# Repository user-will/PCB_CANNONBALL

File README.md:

# REIL INDUSTRIAL - CANNONBALL

A feature-packed ESP32-C3 development board built around the **ESP32-C3-WROOM-02-N4**, designed to be the last board you need for any project — smart home device, RC car, wearable, or anything else you can dream up.

The big pitch: pull a single-cell LiPo or Li-ion from an old vape, plug it into the JST PH connector, and go. The board handles charging, protection, and fuel gauging — no external circuitry needed.

---

## Features

- **MCU** — ESP32-C3-WROOM-02-N4 (RISC-V, 2.4 GHz Wi-Fi + BLE, 4 MB flash)
- **USB protection** — USBLC6-4SC6 TVS diode array on the USB lines
- **Battery charging** — BQ24075RGT linear charger (100 mA default, 500 mA selectable via GPIO)
- **Battery protection** — DW01A + FS8205A dual MOSFET pack (over-charge, over-discharge, short circuit)
- **Battery monitoring** — MAX17048 fuel gauge over I2C with low-battery alert
- **3.3 V regulation** — AP2112K-3.3 LDO
- **Addressable LEDs** — SK6812-EC20 RGB LEDs switched via DMG2301L MOSFET
- **IMU** — LSM6DS3 (6-axis accelerometer + gyroscope, I2C)
- **Temp & humidity** — SHT40 (I2C)
- **Light sensor** — VEML6030 ambient light sensor (I2C)
- **I2C expansion** — JST SH 1.0 mm 4-pin connector (3.3 V, GND, SDA, SCL)
- **Battery connector** — JST PH 2.0 mm 2-pin

---

## Power

| Rail | Source | Voltage | Notes |
|------|--------|---------|-------|
| USB-C | External | 5 V nominal, **6 V max** | Limited by AP2112K-3.3 LDO max input. Do not exceed 6 V on the 5 V pins or USB input. |
| 5V pin (J5/J6) | External or VBUS | 5 V nominal, **6 V max** | Same rail as USB VBUS — feeds the LDO and charger directly. |
| 3V3 pin (J4/J6) | AP2112K-3.3 LDO | **3.3 V exactly** | If powering the board externally via the 3V3 pin (bypassing the LDO), supply a regulated 3.3 V. The ESP32 and all peripherals run at 3.3 V with a ±0.3 V tolerance — do not exceed 3.6 V or drop below 3.0 V. |

---

## Pin Reference

| GPIO | Function | Notes |
|------|----------|-------|
| 3 | MAX17048 alert | Active-low interrupt when battery is low |
| 4 | SK6812 data | Addressable LED data line |
| 5 | LED enable (MOSFET) | Pull **high** to enable LEDs, low to disable |
| 10 | BQ24075 EN1 (charge rate) | Pull **high** to increase charge current from 100 mA to 500 mA |

---

## Bill of Materials

| Reference | Part | Function |
|-----------|------|----------|
| U1 | ESP32-C3-WROOM-02-N4 | Main MCU |
| U2 | BQ24075RGT | Li-ion/LiPo battery charger |
| U3 | MAX17048 | Battery fuel gauge (I2C) |
| U4 | DW01A | Battery protection IC |
| U5 | FS8205A | Dual MOSFET for battery protection |
| U6 | AP2112K-3.3 | 3.3 V LDO regulator |
| U7 | USBLC6-4SC6 | USB ESD/TVS protection |
| U8 | LSM6DS3 | 6-axis IMU (I2C) |
| U9 | SHT40 | Temperature & humidity sensor (I2C) |
| U10 | VEML6030 | Ambient light sensor (I2C) |
| Q3 | 2N7002K | N-channel MOSFET (LED power switch) |
| LED1+ | SK6812-EC20 | Addressable RGB LEDs |

---

## Opening in KiCad

1. Clone or download this repo
2. Open KiCad and select **File → Open Project**
3. Navigate to the repo folder and open `CANNONBALL.kicad_pro`

All schematic symbols and footprints are either embedded in the project files or included in the `jlcpcb.pretty/` and `jlcpcb.kicad_sym` local libraries — no additional library setup required.

---

## Battery Compatibility

Any single-cell LiPo or Li-ion (3.6–4.2 V nominal) will work. The onboard protection circuit guards against:
- Over-charge (> 4.2 V)
- Over-discharge (< 2.5 V)
- Short circuit / over-current

Cells salvaged from vapes, old phones, or RC packs all work fine. Use the JST PH 2.0 mm 2-pin connector (positive on pin 1).

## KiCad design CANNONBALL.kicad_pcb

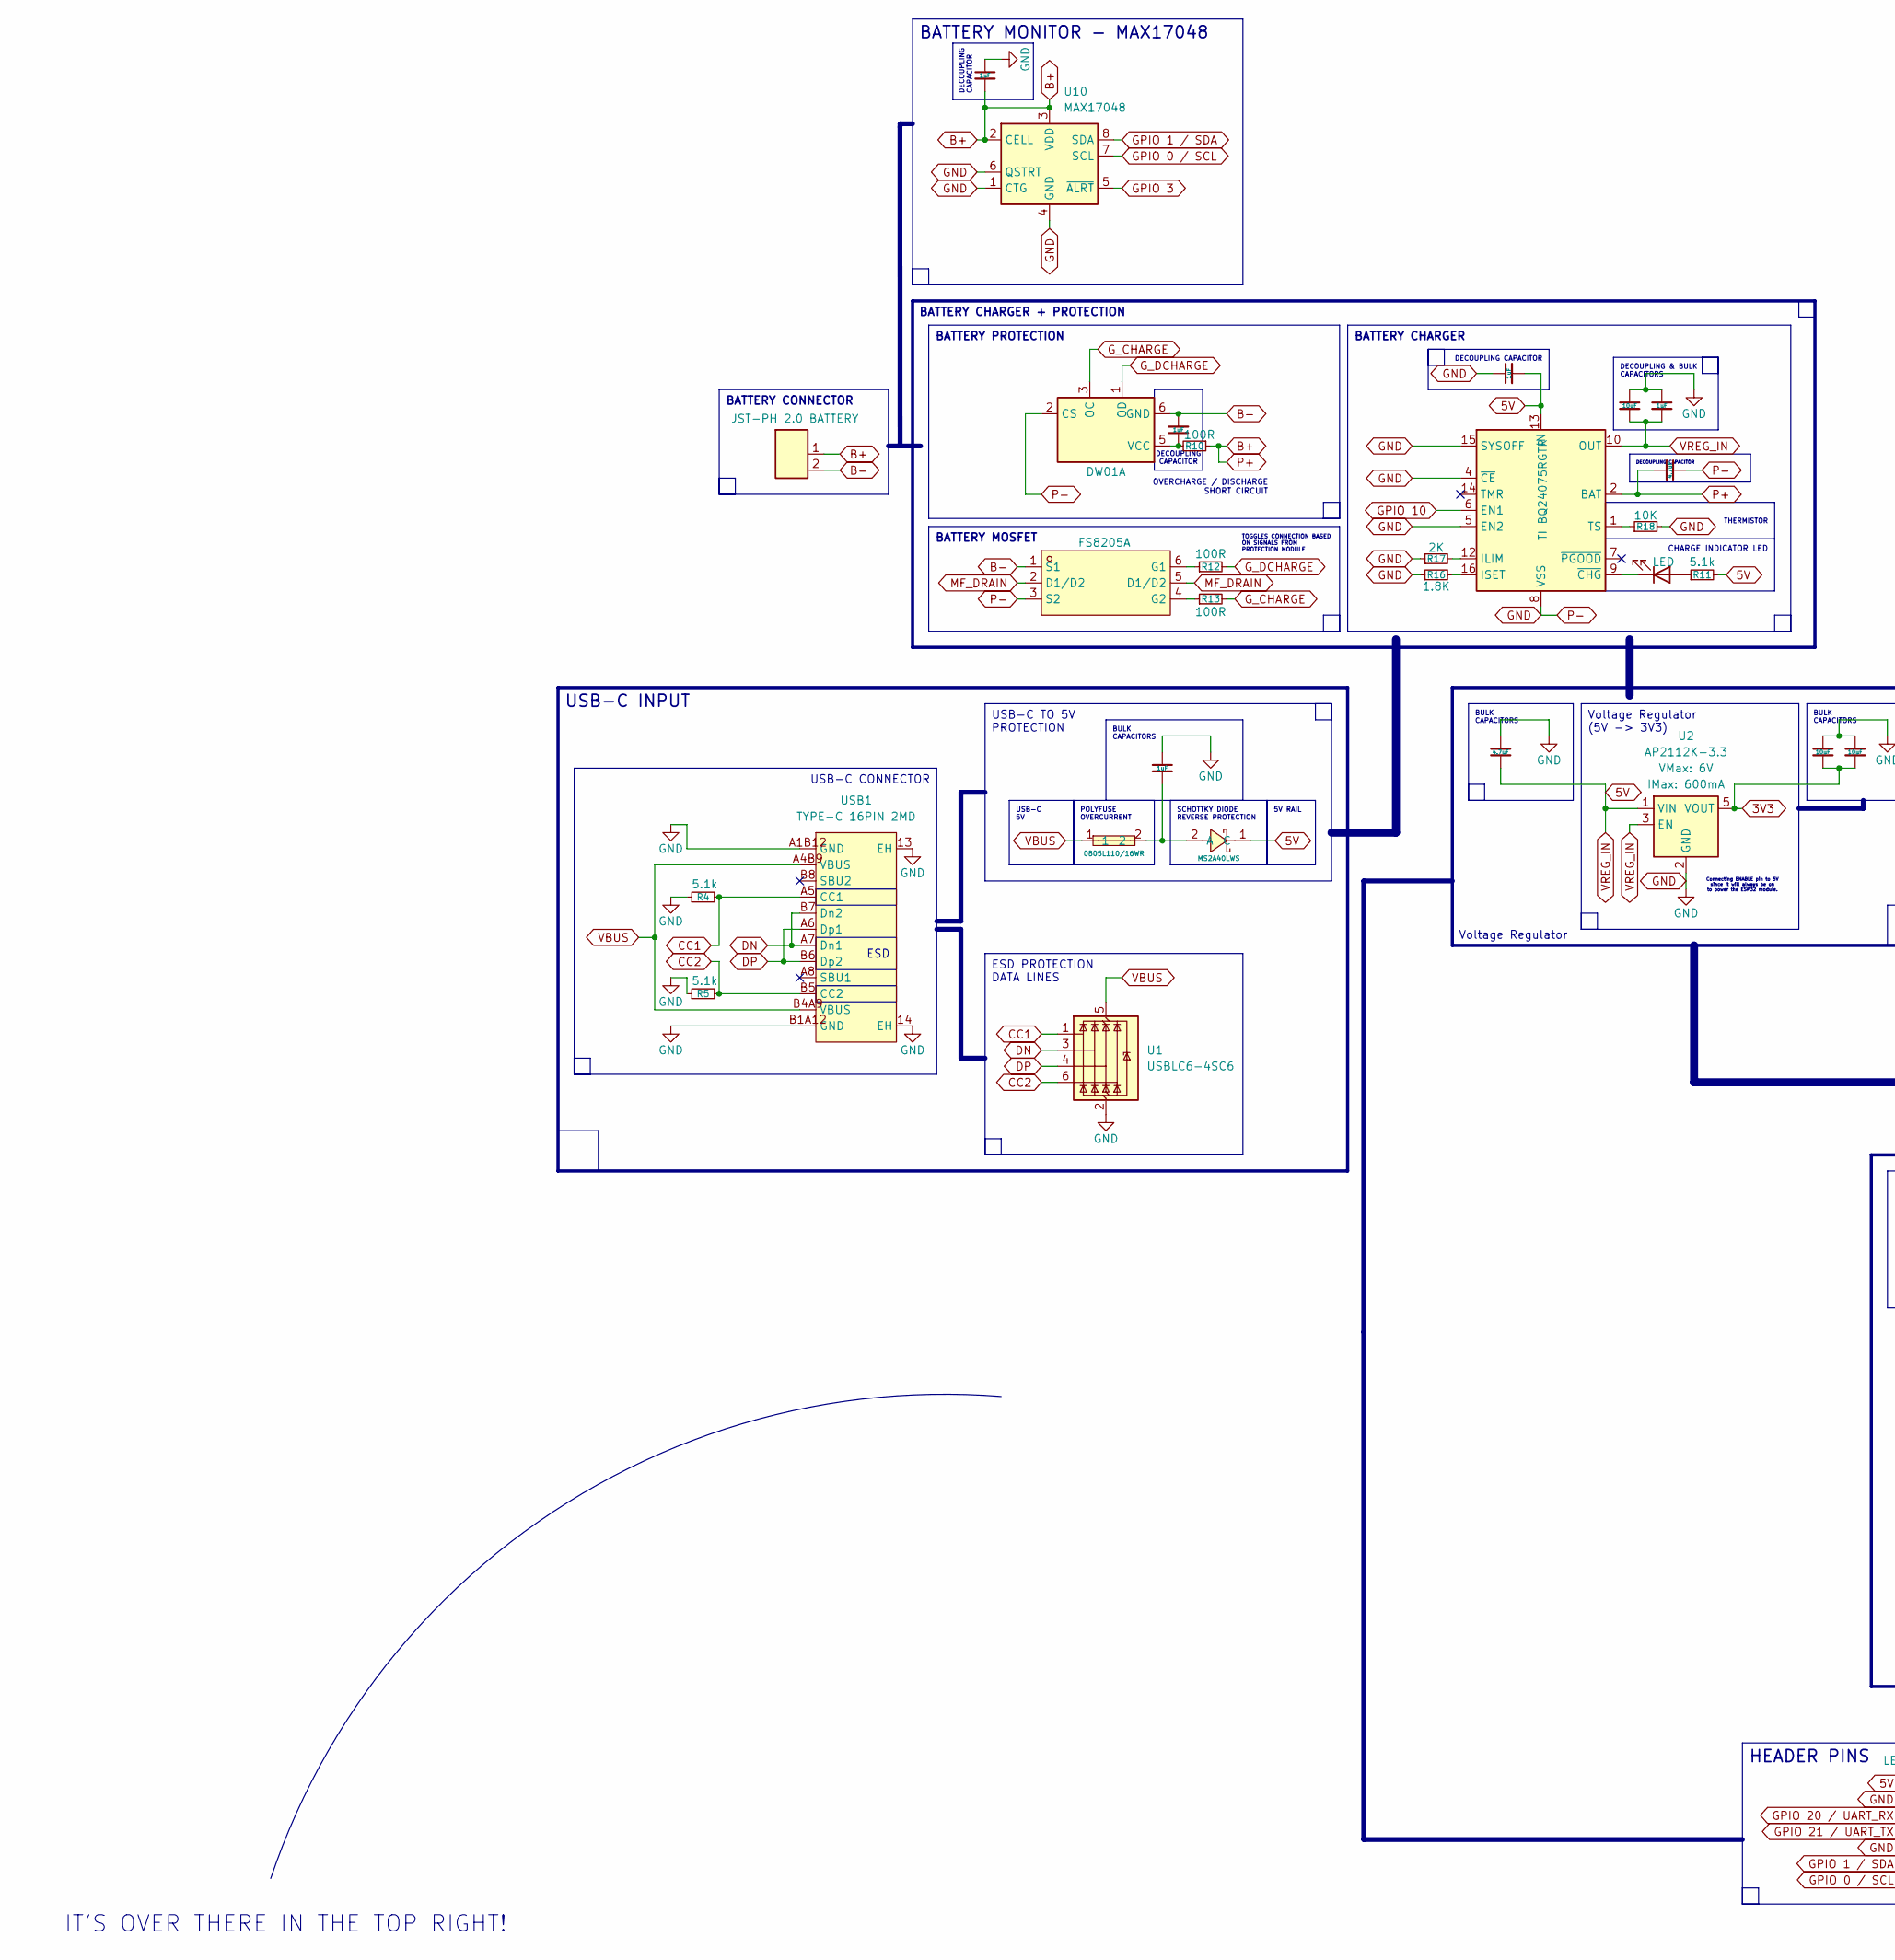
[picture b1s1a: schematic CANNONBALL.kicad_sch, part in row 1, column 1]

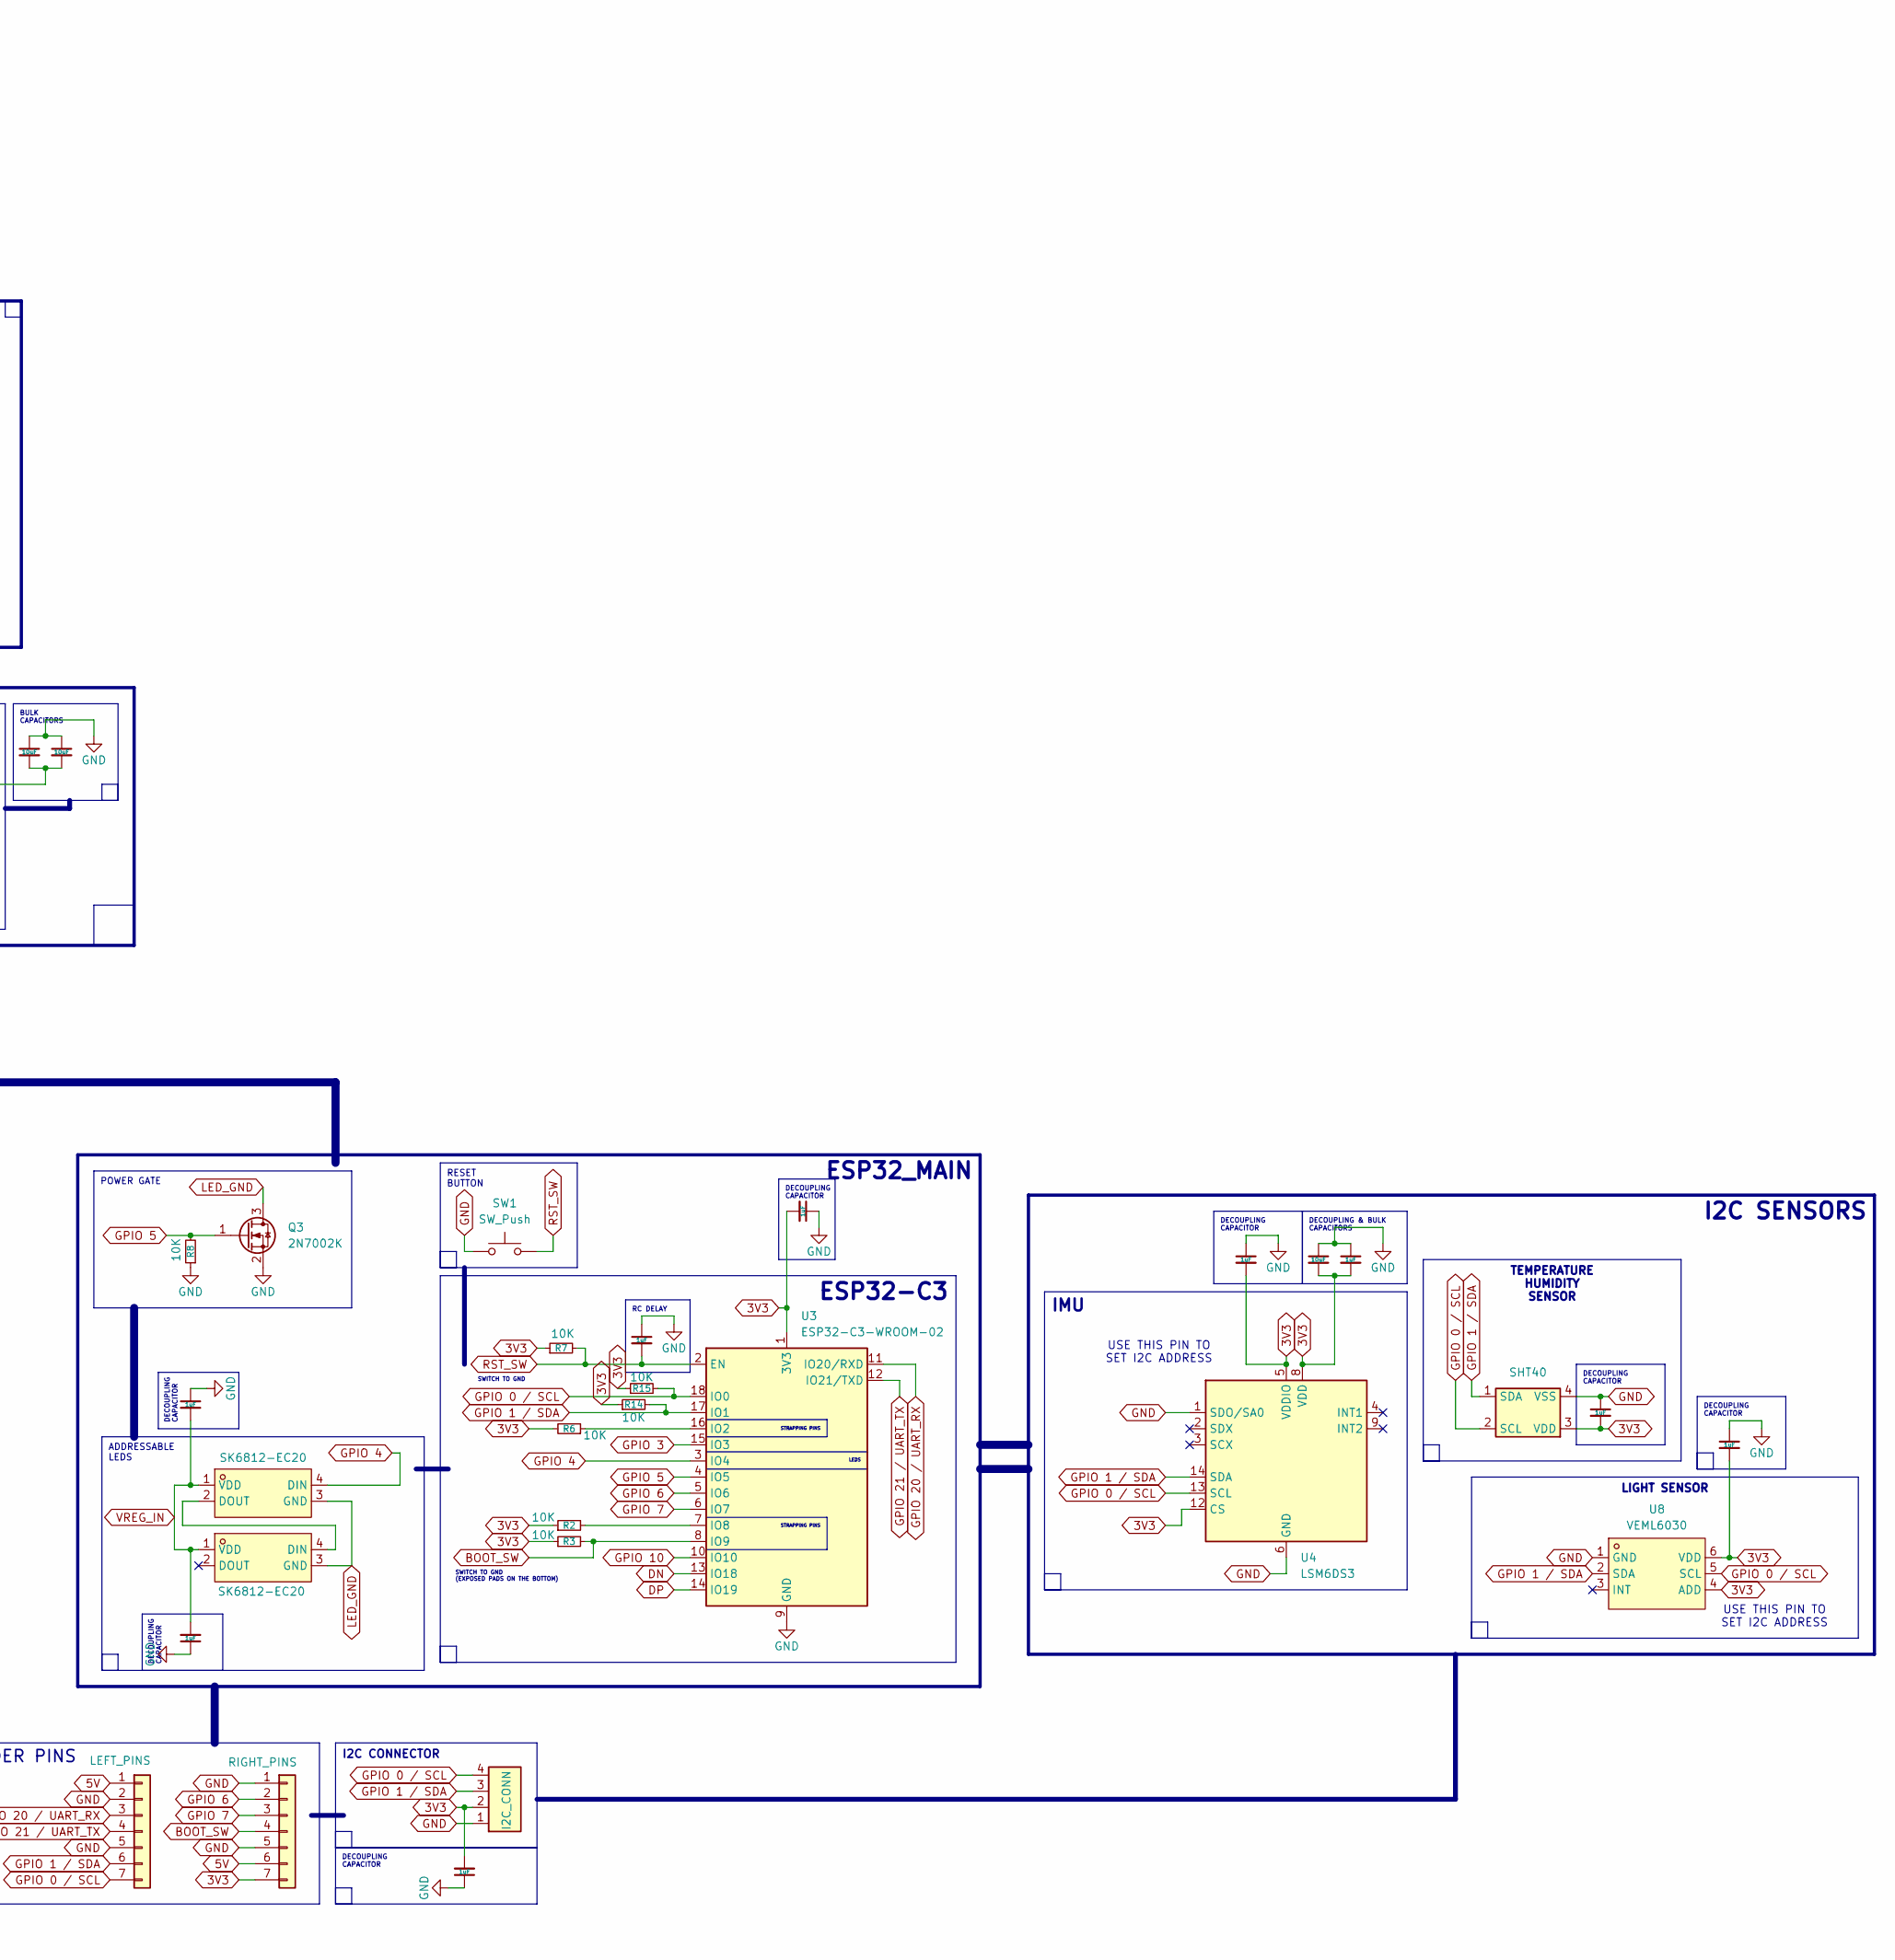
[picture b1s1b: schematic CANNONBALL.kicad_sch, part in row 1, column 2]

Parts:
C1, C3, C10, C11, C12, C14, C16, C18, C20, C21: 1uF; C_0603_1608Metric_Pad1.08x0.95mm_HandSolder
C6, C15: 4.7uF; C_0603_1608Metric_Pad1.08x0.95mm_HandSolder
C8, C9, C17: 10uF; C_0603_1608Metric_Pad1.08x0.95mm_HandSolder
C13: 10uF; C_0402_1005Metric_Pad0.74x0.62mm_HandSolder
C19, C22, C23, C24: 1uF; C_0402_1005Metric_Pad0.74x0.62mm_HandSolder
D2: MS2A40LWS; SOD-323_L1.7-W1.25-LS2.5-RD; MPN MS2A40LWS; LCSC Part C7380001
D4: LED; LED_0603_1608Metric_Pad1.05x0.95mm_HandSolder
F2: 0805L110/16WR; F0805; MPN 0805L110/16WR; LCSC Part C47345575
J3: JST-PH 2.0 BATTERY; CONN-TH_2P-P2.00_XUNPU_WAFER-PH2.0-2PLB
J4: I2C_CONN; CONN-SMD_4P-P1.00_ZX-SH1.0-4PLN
J5: LEFT_PINS; PinHeader_01x07_P2.54mm_Vertical_THT_D1mm
J6: RIGHT_PINS; PinHeader_01x07_P2.54mm_Vertical_THT_D1mm
LED1, LED2: SK6812-EC20; LED-SMD_4P-L2.0-W2.0-BR; MPN SK6812-EC20; LCSC Part C2909058
Q1: FS8205A; SOT-23-6_L2.9-W1.6-P0.95-LS2.8-BR; MPN FS8205A; LCSC Part C2830320
Q3: 2N7002K; SOT-23
R2, R3, R7, R8, R14, R15: 10K; R_0402_1005Metric_Pad0.72x0.64mm_HandSolder
R4, R5, R11: 5.1k; R_0603_1608Metric_Pad0.98x0.95mm_HandSolder
R6, R18: 10K; R_0603_1608Metric_Pad0.98x0.95mm_HandSolder
R10, R12, R13: 100R; R_0603_1608Metric_Pad0.98x0.95mm_HandSolder
R16: 1.8K; R_0603_1608Metric_Pad0.98x0.95mm_HandSolder
R17: 2K; R_0603_1608Metric_Pad0.98x0.95mm_HandSolder
SW1: SW_Push; KEY-SMD_L4.0-W3.0-LS4.9-1
U1: USBLC6-4SC6; SOT-23-6
U2: AP2112K-3.3; SOT23-5
U3: ESP32-C3-WROOM-02
U4: LSM6DS3; LGA-14_2x2mm_P0.35mm_LayoutBorder3x4y
U5: DW01A; SOT-23-6
U6: TI BQ24075RGTR; VQFN-16-1EP_3x3mm_P0.5mm_EP1.6x1.6mm
U7: SHT40; Sensirion_DFN-4_1.5x1.5mm_P0.8mm_SHT4x_NoCentralPad
U8: VEML6030; SENSORS-SMD_VEML6030; MPN VEML6030; LCSC Part C132182
U10: MAX17048; DFN-8_2x2mm_P0.5mm_EP1.2x0.8mm
USB1: TYPE-C 16PIN 2MD; USB-C-SMD_TYPE-C-16PIN-2MD-073; MPN TYPE-C 16PIN 2MD(073); LCSC Part C2765186

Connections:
3V3: C8.2, C9.2, C10.2, C16.2, C17.2, C18.2, C20.2, C21.2, C22.2, J4.2, J6.7, R2.1, R3.1, R6.2, R7.1, R14.1, R15.1, U2.5 (VOUT), U3.1 (3V3), U4.5 (VDDIO), U4.8 (VDD), U4.12 (CS), U7.3 (VDD), U8.4 (ADD), U8.6 (VDD)
5V: C6.2, C12.2, C13.2, C14.2, C19.2, C23.2, D2.1 (C), J5.1, J6.6, LED1.1 (VDD), LED2.1 (VDD), R11.2, U2.1 (VIN), U2.3 (EN), U6.10 (OUT), U6.11 (OUT), U6.13 (IN)
B+: C15.2, C24.2, J3.1, R10.1, U6.2 (BAT), U6.3 (BAT), U10.2 (CELL), U10.3 (VDD)
B-: C11.2, J3.2, Q1.1 (S1), U5.6 (GND)
BOOT_SW: J6.4, R3.2, U3.8 (IO9)
CC1: R4.2, U1.1 (I/O1), USB1.A5 (CC1)
CC2: R5.2, U1.6 (I/O4), USB1.B5 (CC2)
DN: U1.3 (I/O2), U3.13 (IO18), USB1.A7 (Dn1), USB1.B7 (Dn2)
DP: U1.4 (I/O3), U3.14 (IO19), USB1.A6 (Dp1), USB1.B6 (Dp2)
GND: C1.1, C3.1, C6.1, C8.1, C9.1, C10.1, C12.1, C13.1, C14.1, C15.1, C16.1, C17.1, C18.1, C19.1, C20.1, C21.1, C22.1, C23.1, C24.1, J4.1, J5.2, J5.5, J6.1, J6.5, Q1.3 (S2), Q3.2 (S), R4.1, R5.1, R8.1, R16.1, R17.1, R18.2, SW1.1, U1.2 (GND), U2.2 (GND), U3.9 (GND), U3.19 (GND), U4.1 (SDO/SA0), U4.6 (GND), U4.7 (GND), U5.2 (CS), U6.4 (~CE), U6.5 (EN2), U6.8 (VSS), U6.15 (SYSOFF), U6.17 (VSS), U7.4 (VSS), U8.1 (GND), U10.1 (CTG), U10.4 (GND), U10.6 (QSTRT), U10.9 (GND), USB1.13 (EH), USB1.14 (EH), USB1.A1B12 (GND), USB1.B1A12 (GND)
GPIO 0 / SCL: J4.4, J5.7, R15.2, U3.18 (IO0), U4.13 (SCL), U7.2 (SCL), U8.5 (SCL), U10.7 (SCL)
GPIO 1 / SDA: J4.3, J5.6, R14.2, U3.17 (IO1), U4.14 (SDA), U7.1 (SDA), U8.2 (SDA), U10.8 (SDA)
GPIO 3: U3.15 (IO3), U10.5 (~ALRT)
GPIO 4: LED1.4 (DIN), U3.3 (IO4)
GPIO 5: Q3.1 (G), R8.2, U3.4 (IO5)
GPIO 6: J6.2, U3.5 (IO6)
GPIO 7: J6.3, U3.6 (IO7)
GPIO 10: U3.10 (IO10), U6.6 (EN1)
GPIO 20 / UART_RX: J5.3, U3.11 (IO20/RXD)
GPIO 21 / UART_TX: J5.4, U3.12 (IO21/TXD)
G_CHARGE: R13.2, U5.3 (OC)
G_DCHARGE: R12.2, U5.1 (OD)
LED_GND: LED1.3 (GND), LED2.3 (GND), Q3.3 (D)
MF_DRAIN: Q1.2 (D1/D2), Q1.5 (D1/D2)
unnamed: C1.2, D2.2 (A), F2.2
unnamed: D4.2 (A), R11.1
unnamed: D4.1 (K), U6.9 (~CHG)
unnamed: LED1.2 (DOUT), LED2.4 (DIN)
unnamed: Q1.6 (G1), R12.1
unnamed: Q1.4 (G2), R13.1
unnamed: R6.1, U3.16 (IO2)
unnamed: R2.2, U3.7 (IO8)
unnamed: C11.1, R10.2, U5.5 (VCC)
unnamed: R17.2, U6.12 (ILIM)
unnamed: R16.2, U6.16 (ISET)
unnamed: R18.1, U6.1 (TS)
RST_SW: C3.2, R7.2, SW1.2, U3.2 (EN)
VBUS: F2.1, U1.5 (VBUS), USB1.A4B9 (VBUS), USB1.B4A9 (VBUS)

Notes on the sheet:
USE THIS PIN TO SET I2C ADDRESS
SWITCH TO GND
OVERCHARGE / DISCHARGE SHORT CIRCUIT
TOGGLES CONNECTION BASED ON SIGNALS FROM PROTECTION MODULE
IT'S OVER THERE IN THE TOP RIGHT!
SWITCH TO GND (EXPOSED PADS ON THE BOTTOM)
Connecting ENABLE pin to 5V since it will always be on to power the ESP32 module.
BULK CAPACITORS
HEADER PINS
I2C SENSORS
DECOUPLING CAPACITOR
BATTERY PROTECTION
Voltage Regulator
LEDS
IMU
ESP32_MAIN
USB-C TO 5V PROTECTION
ESP32-C3
SCHOTTKY DIODE REVERSE PROTECTION
BATTERY CHARGER + PROTECTION
5V RAIL
USB-C CONNECTOR
I2C CONNECTOR
USB-C 5V
CHARGE INDICATOR LED
DECOUPLING CAPACITOR
STRAPPING PINS
BATTERY CONNECTOR
POWER GATE
LIGHT SENSOR
ESD
RESET BUTTON
BATTERY CHARGER
ESD PROTECTION DATA LINES
POLYFUSE OVERCURRENT
BATTERY MOSFET
ADDRESSABLE LEDS
USB-C INPUT
TEMPERATURE HUMIDITY SENSOR
THERMISTOR

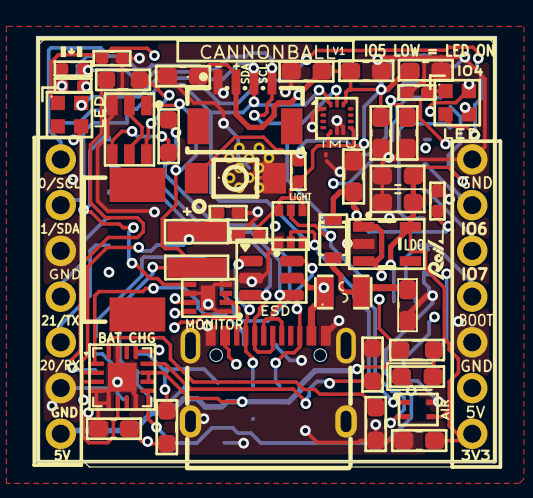
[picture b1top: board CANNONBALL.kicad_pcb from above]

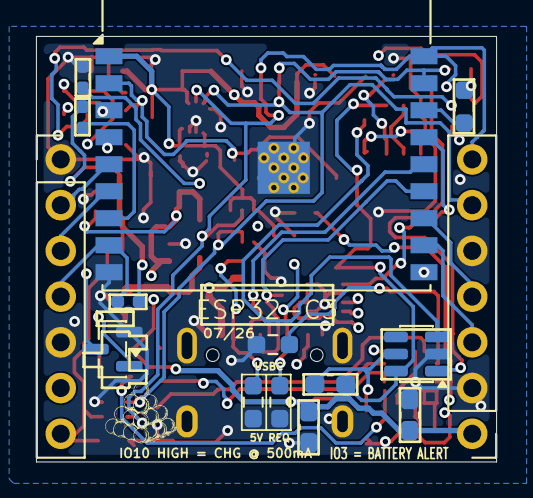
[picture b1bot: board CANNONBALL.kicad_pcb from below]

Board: 4 copper layers, 25.6 x 23.6 mm, 58 parts (15 on the bottom side), 38 nets.

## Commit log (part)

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2026-06-26 kicad-happy review
2026-06-26 reverting not intended changes
